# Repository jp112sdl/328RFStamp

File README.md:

# 328RFStamp

https://user-images.githubusercontent.com/18190139/147872786-335e677a-a8d6-4a60-accb-12a7c5812dc8.mp4

universelle Trägerplatine für ein CC1101 Funkmodul und einen ATmega328P in kleinstmöglicher Abmessung.<br/>
- ISP Anschluss erfolgt über die Pins des CC1101.
- FTDI Pins sind 2mm-RM! 

#### Parts
| Anzahl | Ref | Typ | Bezeichnung |
|----|----|----|----|
1 | U1 | AVR | [ATMega 328P-AU](https://www.reichelt.de/mcu-atmega-avr-risc-32-kb-20-mhz-tqfp-32-atmega-328p-au-p119684.html)
1 | IC1 | RF-Module | [CC1101](https://de.aliexpress.com/item/32852540940.html)
1 | R1 | Widerstand 10k | [RND 0805 10k](https://www.reichelt.de/smd-widerstand-0805-10-kohm-125-mw-1-rnd-0805-1-10k-p183251.html)
1 | R2 | Widerstand 330 | [RND 0805 330](https://www.reichelt.de/smd-widerstand-0805-330-ohm-125-mw-1-rnd-0805-1-330-p183184.html)
3 | C1, C2, C4 |Kondensator 100n |[X7R-G0805 100N](https://www.reichelt.de/smd-vielschicht-keramikkondensator-100n-10-x7r-g0805-100n-p31879.html)
1 | C3 |Kondensator Tantal 10µ |[T491B 10U 16](https://www.reichelt.de/smd-tantal-10-f-16v-125-c-t491a-10u-16-p206441.html)

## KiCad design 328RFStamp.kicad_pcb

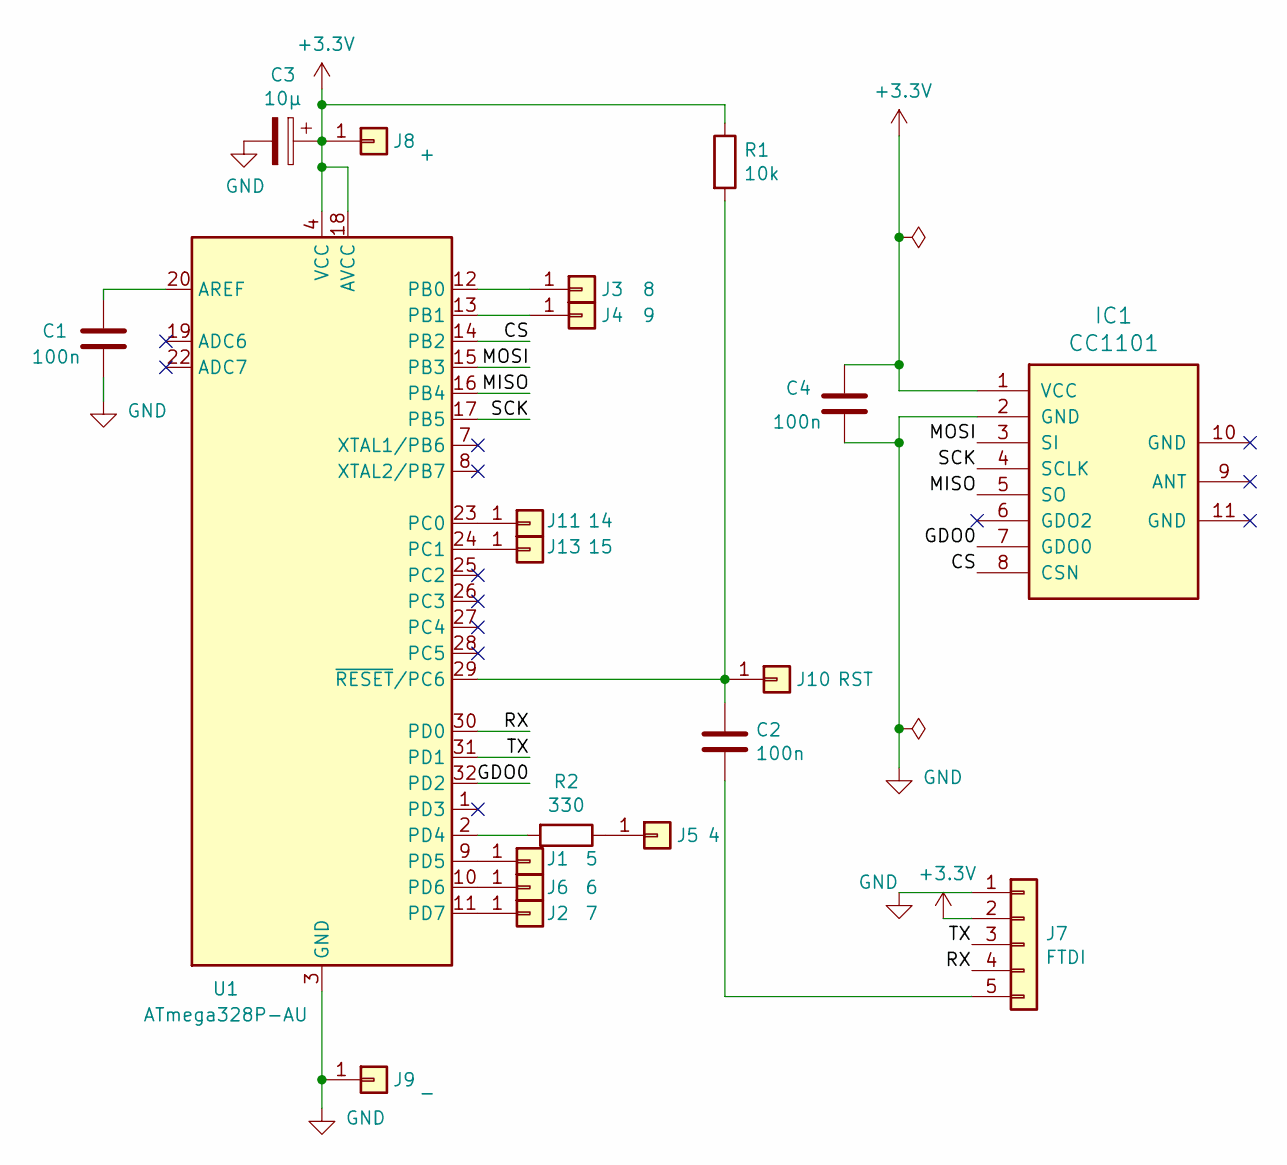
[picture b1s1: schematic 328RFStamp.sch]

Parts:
C1, C2, C4: 100n; C_0805_2012Metric_Pad1.15x1.40mm_HandSolder
C3: 10µ; CP_EIA-3216-18_Kemet-A_Pad1.58x1.35mm_HandSolder
IC1: CC1101; PinHeader_1x08_P2.00mm_Vertical
J1: 5; TestPoint_Pad_D1.5mm
J2: 7; TestPoint_Pad_D1.5mm
J3: 8; TestPoint_Pad_D1.5mm
J4: 9; TestPoint_Pad_D1.5mm
J5: 4; TestPoint_Pad_D1.5mm
J6: 6; TestPoint_Pad_D1.5mm
J7: FTDI; PinHeader_1x05_P2.00mm_Vertical
J8: +; TestPoint_Pad_D1.5mm
J9: -; TestPoint_Pad_D1.5mm
J10: RST; TestPoint_Pad_D1.5mm
J11: 14; TestPoint_Pad_D1.0mm
J13: 15; TestPoint_Pad_D1.0mm
R1: 10k; R_0805_2012Metric_Pad1.15x1.40mm_HandSolder
R2: 330; R_0805_2012Metric_Pad1.15x1.40mm_HandSolder
U1: ATmega328P-AU; TQFP-32_7x7mm_P0.8mm

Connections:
+3V3: C3.1, C4.1, IC1.1 (VCC), J7.2, J8.1, R1.1, U1.4 (VCC), U1.6 (VCC), U1.18 (AVCC)
/CS: IC1.8 (CSN), U1.14 (PB2)
/GDO0: IC1.7 (GDO0), U1.32 (PD2)
/MISO: IC1.5 (SO), U1.16 (PB4)
/MOSI: IC1.3 (SI), U1.15 (PB3)
/RX: J7.4, U1.30 (PD0)
/SCK: IC1.4 (SCLK), U1.17 (PB5)
/TX: J7.3, U1.31 (PD1)
GND: C1.2, C3.2, C4.2, IC1.2 (GND), J7.1, J9.1, U1.3 (GND), U1.5 (GND), U1.21 (GND)
unnamed: C1.1, U1.20 (AREF)
unnamed: C2.1, J10.1, R1.2, U1.29 (~RESET~/PC6)
unnamed: C2.2, J7.5
unnamed: J1.1, U1.9 (PD5)
unnamed: J2.1, U1.11 (PD7)
unnamed: J3.1, U1.12 (PB0)
unnamed: J4.1, U1.13 (PB1)
unnamed: J5.1, R2.1
unnamed: J6.1, U1.10 (PD6)
unnamed: J11.1, U1.23 (PC0)
unnamed: J13.1, U1.24 (PC1)
unnamed: R2.2, U1.2 (PD4)

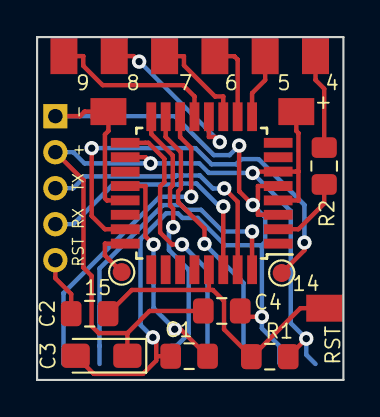
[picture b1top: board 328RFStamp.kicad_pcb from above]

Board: 2 copper layers, 17.0 x 19.0 mm, 20 parts (1 on the bottom side), 21 nets.

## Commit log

2019-10-29 corrected value for C3
2019-10-29 update C3
2019-11-13 add images
2022-01-02 update to KiCad 6
2022-01-02 add blender project
2022-01-02 add 3D shapes
2022-01-02 add blender rendered video animation
2022-01-12 update blender

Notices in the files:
328RFStamp.kicad_pcb:
CC BY-NC-SA 4.0
(c) 2019 jp112sdl
